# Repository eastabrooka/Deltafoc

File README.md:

# BaselineRP2040_MotorController

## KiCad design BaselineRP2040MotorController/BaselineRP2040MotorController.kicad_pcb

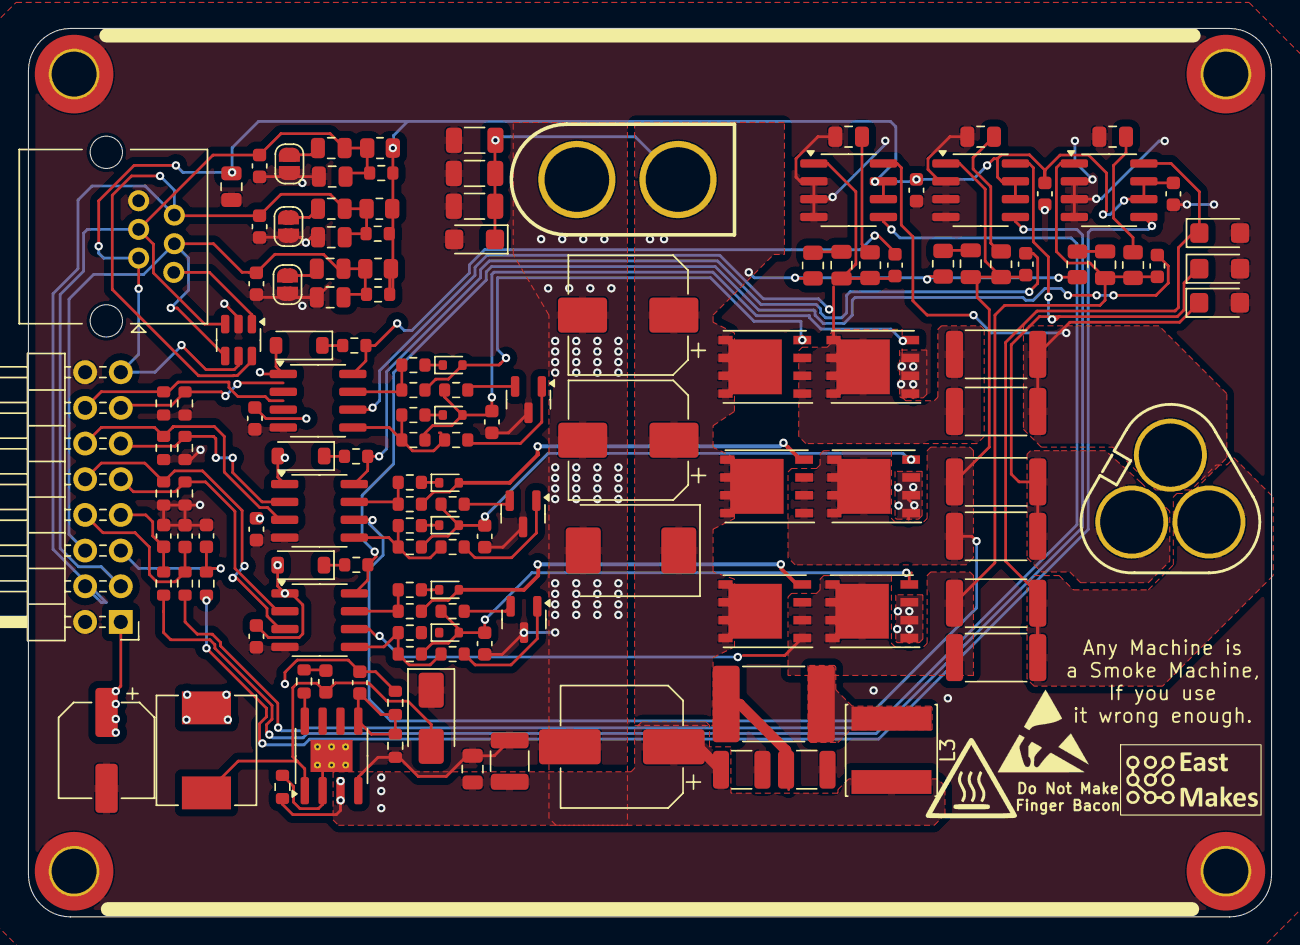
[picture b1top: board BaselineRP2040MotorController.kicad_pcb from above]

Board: 2 copper layers, 88.5 x 63.2 mm, 142 parts (0 on the bottom side), 72 nets.

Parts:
AH1, AH2, AH3: MOSFETSO-8; PowerPAK_SO-8_123
AL1, AL2, AL3: MOSFETSO-8; PowerPAK_SO-8_123
C1, C2, C3: 0; C_0603_1608Metric
C16, C22, C28: 4.7uF 35V; C_0603_1608Metric
C17, C23, C29: DNP; C_0603_1608Metric
C18, C19, C24, C25, C30, C31: C; C_0805_2012Metric
C20, C26, C32: 10uF 35v; C_0603_1608Metric
C21, C27, C33, C55: 100n; C_0603_1608Metric
C34, C35, C38: 2.2uF 100V; C_1206_3216Metric
C36, C37: 220uF 63V solid; CP_Elec_8x10
C39, C42, C45: 22nF; C_0805_2012Metric
C40, C43, C46, C57: 47p; C_0603_1608Metric
C41, C44, C47: C_0805_2012Metric
C48: 10u; C_0805_2012Metric
C49: 47uF 63V solid; CP_Elec_8x10.5
C51, C64, C65: 4.7uF 100V; C_1210_3225Metric
C52: 100nF 100V; C_0805_2012Metric
C60: 220uF 25V; CP_Elec_6.3x7.7
D2, D6, D10: FR107; D_SOD-123
D3, D4, D7, D8, D11, D12: CDBU0130R-HF; D_SOD-523
D5, D9, D13: SMAJ51A; D_SMF
D14: SMDJ51CA; D_SMF
D15: SMAJ51A; D_SMC
D16: SS310; D_SMA
F1: 60V 1.5A hold polyfuse; Fuse_2920_7451Metric
H1, H2, H3, H4: MountingHole_Pad; MountingHole_3.2mm_M3_DIN965_Pad_TopBottom
J2: Encoder 1; RJ14_Connfly_DS1133-S6_Horizontal
J3: 3 Pin XT30 / XT60; MT60-F.G.Y
J4: XT60 Power Connector; CONN-TH_XT60UPB-M
J5: Conn_02x08_Odd_Even; PinHeader_2x08_P2.54mm_Horizontal
JP1, JP2, JP3: SolderJumper_2_Open; SolderJumper-2_P1.3mm_Open_RoundedPad1.0x1.5mm
L1: 47uH; L_Chilisin_BMRB00060612
L3: 68uH 1A; L_Sunlord_SWPA6045S
Q1, Q2, Q3: Q_PNP_BEC; SOT-23
R4, R5, R6: 0; R_0603_1608Metric
R10, R11, R23, R24, R36, R37, R50, R52, R54: 10k; R_0603_1608Metric
R12, R13, R14, R25, R26, R27, R38, R39, R40: 0R; R_0603_1608Metric
R15, R28, R41: 100R; R_0603_1608Metric
R16, R17, R18, R29, R30, R31, R42, R43, R44: 10.2R; R_0603_1608Metric
R19, R20, R32, R33, R45, R46: R; R_0805_2012Metric
R21, R22, R34, R35, R47, R48: 3mΩ; R_2512_6332Metric
R51, R53, R55: R_0805_2012Metric
R56: 30mΩ 5%; R_0603_1608Metric
R57: 10Ω; R_0603_1608Metric
R58: 300k; R_0603_1608Metric
R59: 21.5k; R_0603_1608Metric
U5, U7, U9: EG3113; SOIC-8_3.9x4.9mm_P1.27mm
U6, U8, U10: INA240A1D; SOIC-8_3.9x4.9mm_P1.27mm
U11: USBLC6-4SC6; SOT-23-6
U13: TX4139; SOIC-8-1EP_3.9x4.9mm_P1.27mm_EP2.29x3mm_ThermalVias

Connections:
+3V3: C21.1, C27.1, C33.1, C48.2, J2.2, J5.15, R50.1, R51.1, R52.1, R53.1, R54.1, R55.1, U6.6 (V+), U6.7 (REF1), U8.6 (V+), U8.7 (REF1), U10.6 (V+), U10.7 (REF1), U11.5 (VBUS)
+12V: C16.2, C22.2, C28.2, C57.1, C60.1, D2.2 (A), D6.2 (A), D10.2 (A), J5.1, L1.2, R58.2, U5.1 (VCC), U7.1 (VCC), U9.1 (VCC)
/BLDC Power Control/Motor Phase U/A_N: D5.1 (A1), J3.1, R21.2, R22.2, U6.8 (+)
/BLDC Power Control/Motor Phase U/A_P: AH1.1 (S), AL1.3 (D), C18.2, C20.1, R20.1, R21.1, R22.1, U5.6 (VS), U6.1 (-)
/BLDC Power Control/Motor Phase V/A_N: D9.1 (A1), J3.2, R34.2, R35.2, U8.8 (+)
/BLDC Power Control/Motor Phase V/A_P: AH2.1 (S), AL2.3 (D), C24.2, C26.1, R33.1, R34.1, R35.1, U7.6 (VS), U8.1 (-)
/BLDC Power Control/Motor Phase X/A_N: D13.1 (A1), J3.3, R47.2, R48.2, U10.8 (+)
/BLDC Power Control/Motor Phase X/A_P: AH3.1 (S), AL3.3 (D), C30.2, C32.1, R46.1, R47.1, R48.1, U9.6 (VS), U10.1 (-)
/CurrentSense1: C2.2, J5.7, R5.2
/CurrentSense2: C1.2, J5.8, R4.2
/CurrentSense3: C3.2, J5.5, R6.2
/Encoder CS: C42.1, C43.2, C44.2, J2.4, J5.3, R52.2, R53.2, U11.3 (I/O2)
/Encoder RX: C39.2, C40.2, C41.2, J2.3, J5.6, R50.2, R51.2, U11.4 (I/O3)
/Encoder SCK: C45.1, C46.2, C47.2, J2.5, J5.4, R54.2, R55.2, U11.6 (I/O4)
/Hall Effect Encoders/TH_MOTOR1: J2.1, U11.1 (I/O1)
/PWM H U: J5.13, R10.2, U5.2 (HIN)
/PWM H V: J5.11, R23.2, U7.2 (HIN)
/PWM H X: J5.9, R36.2, U9.2 (HIN)
/PWM L U: J5.14, R11.2, U5.3 (~LIN)
/PWM L V: J5.12, R24.2, U7.3 (~LIN)
/PWM L X: J5.10, R37.2, U9.3 (~LIN)
/Power Filtering/BS: R57.1, U13.8 (BS)
/Power Filtering/FB: C57.2, R58.1, R59.2, U13.5 (FB)
/Power Filtering/SW: C55.1, D16.2 (A), L1.1, U13.1 (SW)
GND: AL1.1 (S), AL2.1 (S), AL3.1 (S), C1.1, C2.1, C3.1, C16.1, C17.1, C19.2, C21.2, C22.1, C23.1, C25.2, C27.2, C28.1, C29.1, C31.2, C33.2, C34.2, C35.2, C36.2, C37.2, C38.2, C40.1, C41.1, C43.1, C44.1, C46.1, C47.1, C48.1, C49.2, C51.2, C52.2, C60.2, C64.2, C65.2, D5.2 (A2), D9.2 (A2), D13.2 (A2), D14.2 (A2), D15.2 (A2), D16.1 (K), H1.1, H2.1, H3.1, H4.1, J2.6, J4.1, J5.2, J5.16, JP1.1 (A), JP2.1 (A), JP3.1 (A), Q1.3 (C), Q2.3 (C), Q3.3 (C), R10.1, R11.1, R23.1, R24.1, R36.1, R37.1, R59.1, U5.4 (COM), U6.2 (GND), U6.3 (REF2), U6.4 (GND), U7.4 (COM), U8.2 (GND), U8.3 (REF2), U8.4 (GND), U9.4 (COM), U10.2 (GND), U10.3 (REF2), U10.4 (GND), U11.2 (GND), U13.4 (GND)
unnamed: AH1.2 (G), D3.2 (A), R16.2
unnamed: AH2.2 (G), D7.2 (A), R29.2
unnamed: AH3.2 (G), D11.2 (A), R42.2
unnamed: AL1.2 (G), C17.2, D4.2 (A), R17.2, R18.2
unnamed: AL2.2 (G), C23.2, D8.2 (A), R30.2, R31.2
unnamed: AL3.2 (G), C29.2, D12.2 (A), R43.2, R44.2
unnamed: C18.1, R19.2
unnamed: C19.1, R20.2
unnamed: C24.1, R32.2
unnamed: C25.1, R33.2
unnamed: C30.1, R45.2
unnamed: C31.1, R46.2
unnamed: C55.2, R57.2
unnamed: D2.1 (K), R12.1
unnamed: D3.1 (K), R13.2
unnamed: D4.1 (K), R14.2
unnamed: D6.1 (K), R25.1
unnamed: D7.1 (K), R26.2
unnamed: D8.1 (K), R27.2
unnamed: D10.1 (K), R38.1
unnamed: D11.1 (K), R39.2
unnamed: D12.1 (K), R40.2
unnamed: F1.2, L3.1
unnamed: C39.1, JP1.2 (B)
unnamed: C42.2, JP2.2 (B)
unnamed: C45.2, JP3.2 (B)
unnamed: Q1.1 (B), R15.2
unnamed: Q1.2 (E), R18.1
unnamed: Q2.1 (B), R28.2
unnamed: Q2.2 (E), R31.1
unnamed: Q3.1 (B), R41.2
unnamed: Q3.2 (E), R44.1
unnamed: R4.1, U6.5
unnamed: R5.1, U8.5
unnamed: R6.1, U10.5
unnamed: R56.1, U13.2 (ILIM), U13.9 (ILIM)
unnamed: R13.1, R16.1, U5.7 (HO)
unnamed: R14.1, R15.1, R17.1, U5.5 (LO)
unnamed: C20.2, R12.2, U5.8 (VB)
unnamed: R26.1, R29.1, U7.7 (HO)
unnamed: R27.1, R28.1, R30.1, U7.5 (LO)
unnamed: C26.2, R25.2, U7.8 (VB)
unnamed: R39.1, R42.1, U9.7 (HO)
unnamed: R40.1, R41.1, R43.1, U9.5 (LO)
unnamed: C32.2, R38.2, U9.8 (VB)
VMOT: C49.1, C51.1, C52.1, C65.1, L3.2, R56.2, U13.3 (VIN)
VMOT_PWR: AH1.3 (D), AH2.3 (D), AH3.3 (D), C34.1, C35.1, C36.1, C37.1, C38.1, C64.1, D14.1 (A1), D15.1 (A1), F1.1, J4.2, R19.1, R32.1, R45.1

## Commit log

2024-08-28 Back from Cruise - Upload and Squash.
2024-08-28 Update Submodule
2024-08-28 Change Mosfet Footprint.
2024-08-28 Continue Work
2024-08-28 Drop some features.
2024-08-28 Just before dropping the self build of the 2040
2024-08-28 Erhhhhrh
2024-08-28 Going to take a break.
2024-09-06 Release for Review
2024-09-07 Generate PDF
2024-09-07 Post Feedback Changes.
2024-09-07 Should have been a 4 layer board.
2024-09-07 Graphics.
2024-09-07 Mounting points
2024-09-08 Make a cut down board.
2024-09-08 MinMax
2024-09-08 Heh - Super cut down.
2024-09-08 Update with Text
2024-09-08 Generate Gerbers
2024-09-11 Make Bom
